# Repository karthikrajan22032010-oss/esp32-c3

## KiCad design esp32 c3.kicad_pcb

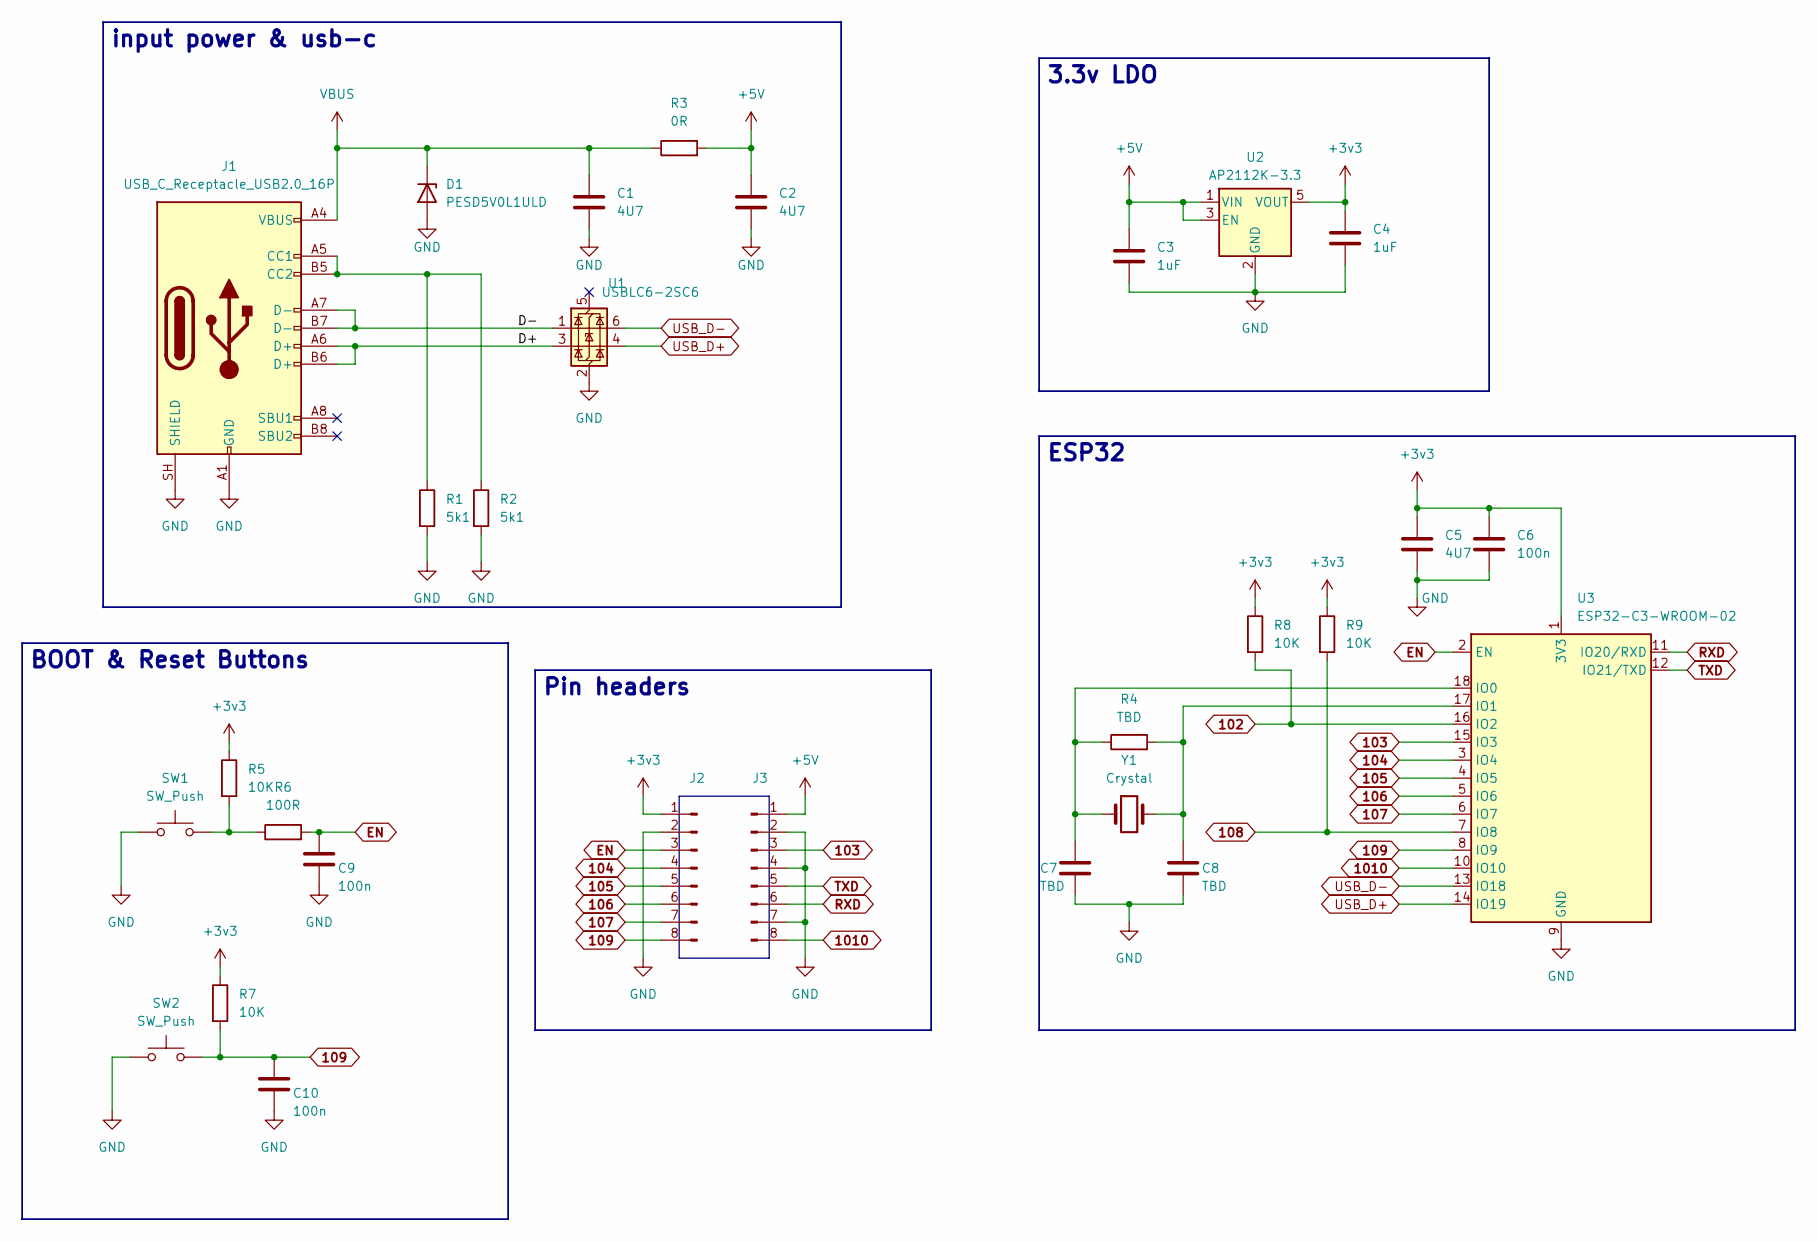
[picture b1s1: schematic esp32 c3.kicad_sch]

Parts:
C1, C2, C5: 4U7; C_0805_2012Metric
C3, C4: 1uF; C_0805_2012Metric
C6, C9, C10: 100n; C_0402_1005Metric
C7, C8: TBD; C_0201_0603Metric_Pad0.64x0.40mm_HandSolder
D1: PESD5V0L1ULD; D_SOD-882D
J1: USB_C_Receptacle_USB2.0_16P; USB_C_Receptacle_G-Switch_GT-USB-7010ASV
J2, J3: Conn_01x08_Pin; PinHeader_1x08_P2.54mm_Vertical
R1, R2: 5k1; R_0402_1005Metric
R3: 0R; R_0805_2012Metric
R4: TBD; R_0201_0603Metric
R5, R7, R8, R9: 10K; R_0402_1005Metric
R6: 100R; R_0402_1005Metric
SW1, SW2: SW_Push; SW_SPST_B3U-1000P
U1: USBLC6-2SC6; SOT-23-6
U2: AP2112K-3.3; SOT-23-5
U3: ESP32-C3-WROOM-02
Y1: Crystal; Crystal_SMD_3215-2Pin_3.2x1.5mm

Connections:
102: R8.2, U3.16 (IO2)
103: J3.3, U3.15 (IO3)
104: J2.4, U3.3 (IO4)
105: J2.5, U3.4 (IO5)
106: J2.6, U3.5 (IO6)
107: J2.7, U3.6 (IO7)
108: R9.2, U3.7 (IO8)
109: C10.1, J2.8, R7.2, SW2.2, U3.8 (IO9)
1010: J3.8, U3.10 (IO10)
+3v3: C4.1, C5.1, C6.1, J2.1, R5.1, R7.1, R8.1, R9.1, U2.5 (VOUT), U3.1 (3V3)
+5V: C2.1, C3.1, J3.1, R3.2, U2.1 (VIN), U2.3 (EN)
/D+: J1.A6 (D+), J1.B6 (D+), U1.3 (I/O2)
/D-: J1.A7 (D-), J1.B7 (D-), U1.1 (I/O1)
EN: C9.1, J2.3, R6.2, U3.2 (EN)
GND: C1.2, C2.2, C3.2, C4.2, C5.2, C6.2, C7.2, C8.2, C9.2, C10.2, D1.2 (A), J1.A1 (GND), J1.A12 (GND), J1.B1 (GND), J1.B12 (GND), J1.SH (SHIELD), J2.2, J3.2, J3.4, J3.7, R1.2, R2.2, SW1.1, SW2.1, U1.2 (GND), U2.2 (GND), U3.9 (GND), U3.19 (GND)
unnamed: J1.A5 (CC1), J1.B5 (CC2), R1.1, R2.1
unnamed: R5.2, R6.1, SW1.2
unnamed: C7.1, R4.1, U3.18 (IO0), Y1.1
unnamed: C8.1, R4.2, U3.17 (IO1), Y1.2
RXD: J3.6, U3.11 (IO20/RXD)
TXD: J3.5, U3.12 (IO21/TXD)
USB_D+: U1.4 (I/O2), U3.14 (IO19)
USB_D-: U1.6 (I/O1), U3.13 (IO18)
VBUS: C1.1, D1.1 (K), J1.A4 (VBUS), J1.A9 (VBUS), J1.B4 (VBUS), J1.B9 (VBUS), R3.1

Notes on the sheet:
ESP32
Pin headers
3.3v LDO
BOOT & Reset Buttons
input power & usb-c

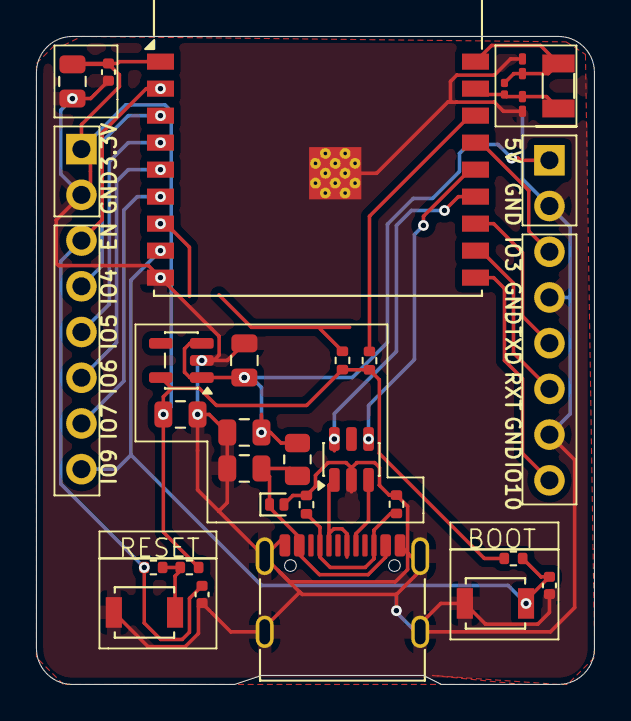
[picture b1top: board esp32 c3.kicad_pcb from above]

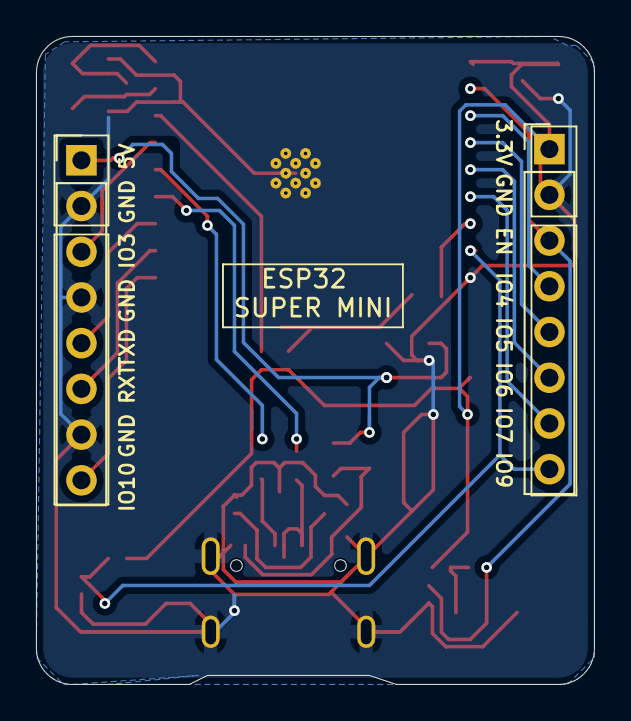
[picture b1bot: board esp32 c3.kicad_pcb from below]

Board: 2 copper layers, 31.0 x 36.0 mm, 29 parts (2 on the bottom side), 24 nets.
